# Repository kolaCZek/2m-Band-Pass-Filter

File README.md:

# 2m Band Pass Filter

[OSHPark Project](https://oshpark.com/shared_projects/Gucpk6xE)

## Characteristics

## BOM

 - 2x [1008 10nH](https://www.tme.eu/en/details/cw1008-10/smd-coils/ferrocore/)
 - 1x [1008 330nH](https://www.tme.eu/en/details/cw1008-330/smd-coils/ferrocore/)
 - 2x [0805 120pF](https://www.tme.eu/en/details/cc0805jrnpo9121/0805-mlcc-smd-capacitors/yageo/cc0805jrnpo9bn121/)
 - 1x [0805 3.6pF](https://www.tme.eu/en/details/cl21c3r6bbaannc/0805-mlcc-smd-capacitors/samsung/)
 - 2x [SMA](https://www.ebay.com/sch/i.html?_from=R40&_sacat=0&_nkw=sma+female+pcb+edge+mount&rt=nc&LH_BIN=1)
 - 1x [PCB](https://oshpark.com/shared_projects/Gucpk6xE)

## Other Projects

 - [2m/70cm Diplexer](https://github.com/kolaCZek/2m-70cm-Diplexer)
 - [FM Trap](https://github.com/kolaCZek/FM-Trap)
 - [Bias-T](https://github.com/kolaCZek/Bias-T)

## License

[Apache License Version 2.0](./LICENSE)

## Donate

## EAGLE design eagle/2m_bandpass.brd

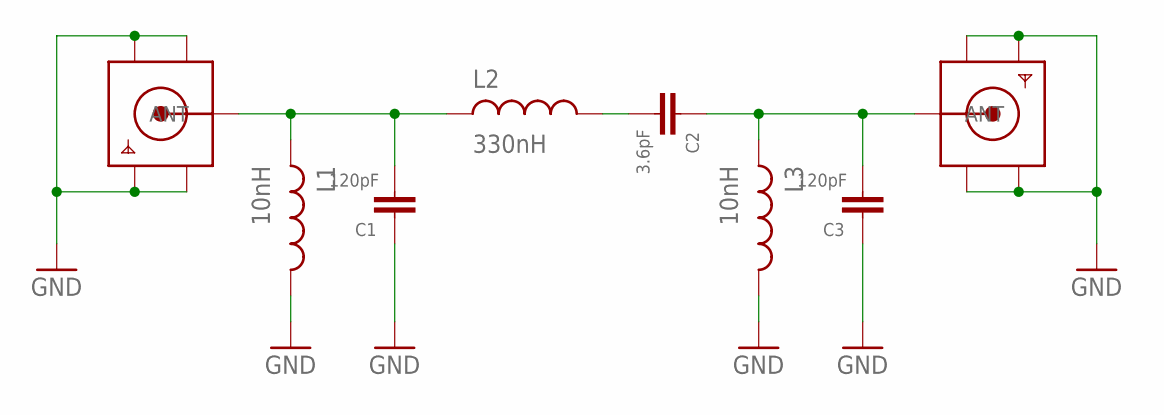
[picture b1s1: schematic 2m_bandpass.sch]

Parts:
C1, C3: 120pF; 0805
C2: 3.6pF; 0805
L1, L3: 10nH; 1008INDUCTOR
L2: 330nH; 1008INDUCTOR
X1, X2: SMACONNECTOR_EDGE; SMA_EDGELAUNCH

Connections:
GND: C1.P$2, C3.P$2, L1.P$2, L3.P$2, X1.GND@1 (GND4), X1.GND@2 (GND3), X1.GND@3 (GND2), X1.GND@4 (GND1), X2.GND@1 (GND4), X2.GND@2 (GND3), X2.GND@3 (GND2), X2.GND@4 (GND1)
unnamed: C1.P$1, L1.P$1, L2.P$1, X1.P (ANT)
unnamed: C2.P$2, C3.P$1, L3.P$1, X2.P (ANT)
unnamed: C2.P$1, L2.P$2

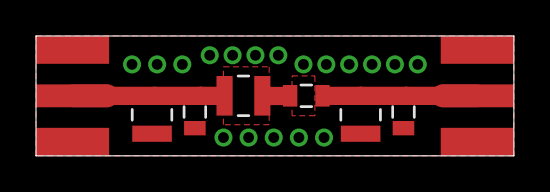
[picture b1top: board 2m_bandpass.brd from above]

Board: 2 copper layers, 26.5 x 6.7 mm, 8 parts (0 on the bottom side), 4 nets.

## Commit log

2018-02-15 Init commit
2018-02-15 Readme
2018-02-15 Readme - OSHPark
2018-02-15 Readme - Other projects
2022-01-25 Add ko-fi button
2022-01-25 Remove LTC/BTC
